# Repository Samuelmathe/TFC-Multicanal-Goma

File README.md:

# TFC Multicanal Goma

Système embarqué IoT de sous-comptage électrique multicanal (ESP32),
développé dans le cadre d'un Travail de Fin de Cycle (ULPGL) : un boîtier
mesure et facture séparément la consommation électrique de plusieurs
locataires branchés sur une même installation, avec coupure automatique par
crédit prépayé et consultation via une application mobile Flutter.

## État du projet

- **Maquette physique** : construite, soudée sur carte perforée et
  **validée sur matériel réel** (4 canaux : 1 bailleur + 3 locataires,
  capteurs simulés par des potentiomètres). C'est cette maquette qui a servi
  à la validation présentée dans le mémoire.
- **Application mobile Flutter** : développée et testée en conditions
  réelles (connexion Wi-Fi à l'ESP32 depuis un téléphone Android).
- **PCB (circuit imprimé, 8 canaux, capteurs ACS712/ZMPT101B réels)** :
  conçu sous KiCad (dossier `kicad/`) — **routage non terminé, il reste 10
  pistes à tracer** ; non encore fabriqué ni assemblé. Le firmware cible pour
  ce PCB (`firmware_pcb_capteurs_reels/`) est écrit et compile, mais n'a donc
  pas pu être testé sur le matériel réel.

## Structure du dépôt

```
firmware/                      -> firmware de la maquette physique (4 canaux,
                                   potentiometres) - construit et valide
firmware_pcb_capteurs_reels/    -> firmware cible pour le PCB (8 canaux,
                                    ACS712 + ZMPT101B) - PCB pas encore
                                    fabrique, code non teste sur materiel reel
application/                     -> application mobile Flutter (Android/iOS)
kicad/                            -> conception du circuit imprime (PCB, 8 canaux)
rapport/                           -> memoire de TFC
presentation/                       -> support de soutenance
```

Chaque dossier de firmware a son propre `README.md` avec le détail de ce qui
a été testé ou non.

## Démarrer

- Firmware maquette : `cd firmware && pio run --target upload` (ESP32 branché
  en USB) — voir `GUIDE_ASSEMBLAGE_ET_FLASH.md` et `GUIDE_MAQUETTE_BOITIER.md`
  à la racine pour le montage physique.
- Application mobile : `cd application && flutter run` (ou `build_apk.sh`
  pour générer un APK).

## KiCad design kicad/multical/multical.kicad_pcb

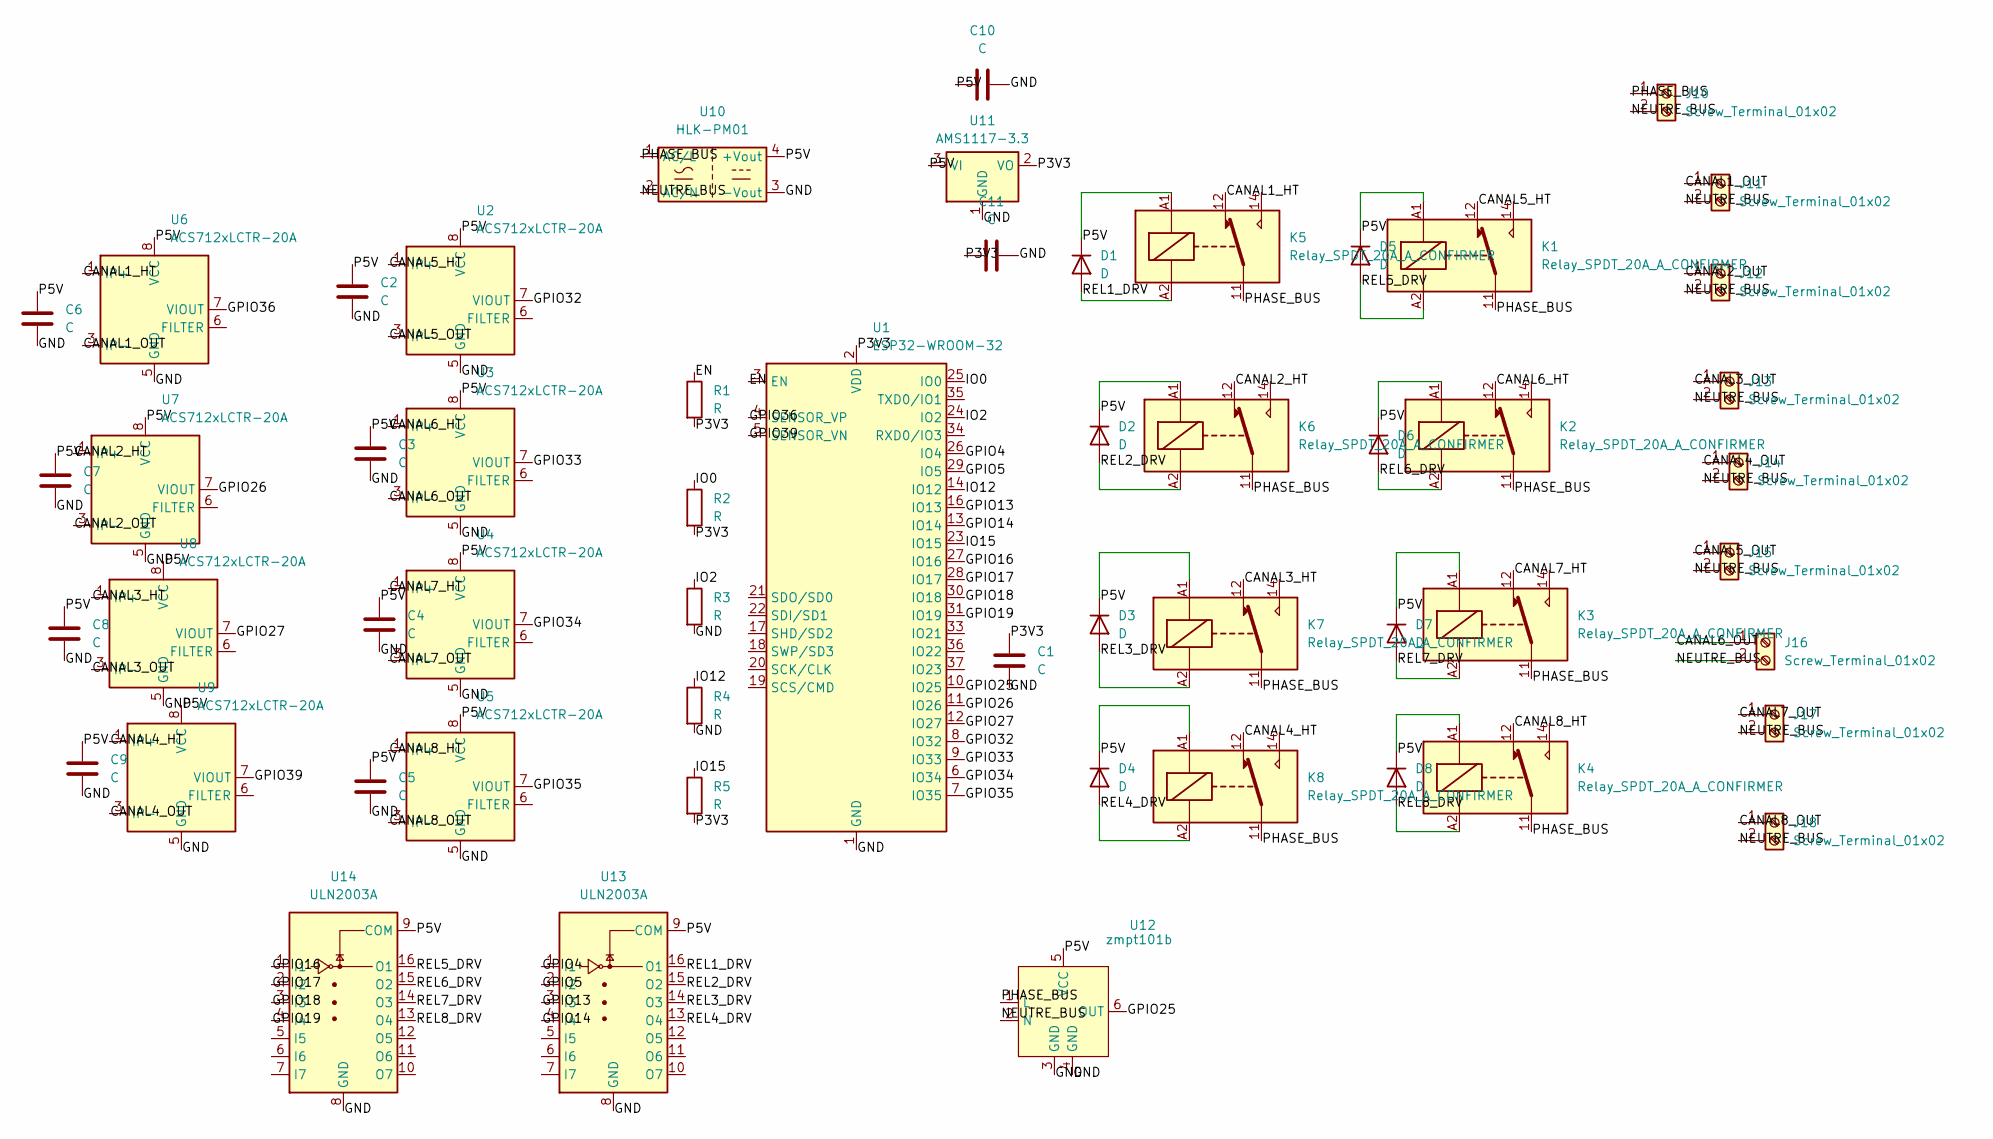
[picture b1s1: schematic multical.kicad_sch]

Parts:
C1, C2, C3, C4, C5, C6, C7, C8, C9: C; C_Disc_D5.0mm_W2.5mm_P5.00mm
C10, C11: C; CP_Radial_D5.0mm_P2.00mm
D1, D2, D3, D4, D5, D6, D7, D8: D; D_DO-41_SOD81_P7.62mm_Horizontal
J10, J11, J12, J13, J14, J15, J16, J17, J18: Screw_Terminal_01x02; TerminalBlock_MaiXu_MX126-5.0-02P_1x02_P5.00mm
K1, K2, K3, K4, K5, K6, K7, K8: Relay_SPDT_20A_A_CONFIRMER; Relay_SPDT_Hongfa_JQC-3FF_0XX-1Z
R1, R2, R3, R4, R5: R; R_Axial_DIN0207_L6.3mm_D2.5mm_P10.16mm_Horizontal
U1: ESP32-WROOM-32
U2, U3, U4, U5, U6, U7, U8, U9: ACS712xLCTR-20A; SOIC-8_3.9x4.9mm_P1.27mm
U10: HLK-PM01; Converter_ACDC_Hi-Link_HLK-PMxx
U11: AMS1117-3.3; SOT-223-3_TabPin2
U12: zmpt101b; PinHeader_1x06_P2.54mm_Vertical
U13, U14: ULN2003A; DIP-16_W7.62mm

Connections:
/CANAL1_HT: K5.12, U6.1 (IP+), U6.2 (IP+)
/CANAL1_OUT: J11.1, U6.3 (IP-), U6.4 (IP-)
/CANAL2_HT: K6.12, U7.1 (IP+), U7.2 (IP+)
/CANAL2_OUT: J12.1, U7.3 (IP-), U7.4 (IP-)
/CANAL3_HT: K7.12, U8.1 (IP+), U8.2 (IP+)
/CANAL3_OUT: J13.1, U8.3 (IP-), U8.4 (IP-)
/CANAL4_HT: K8.12, U9.1 (IP+), U9.2 (IP+)
/CANAL4_OUT: J14.1, U9.3 (IP-), U9.4 (IP-)
/CANAL5_HT: K1.12, U2.1 (IP+), U2.2 (IP+)
/CANAL5_OUT: J15.1, U2.3 (IP-), U2.4 (IP-)
/CANAL6_HT: K2.12, U3.1 (IP+), U3.2 (IP+)
/CANAL6_OUT: J16.1, U3.3 (IP-), U3.4 (IP-)
/CANAL7_HT: K3.12, U4.1 (IP+), U4.2 (IP+)
/CANAL7_OUT: J17.1, U4.3 (IP-), U4.4 (IP-)
/CANAL8_HT: K4.12, U5.1 (IP+), U5.2 (IP+)
/CANAL8_OUT: J18.1, U5.3 (IP-), U5.4 (IP-)
/EN: R1.1, U1.3 (EN)
/GND: C1.2, C2.2, C3.2, C4.2, C5.2, C6.2, C7.2, C8.2, C9.2, C10.2, C11.2, R3.2, R4.2, U1.1 (GND), U1.15 (GND), U1.38 (GND), U1.39 (GND), U2.5 (GND), U3.5 (GND), U4.5 (GND), U5.5 (GND), U6.5 (GND), U7.5 (GND), U8.5 (GND), U9.5 (GND), U10.3 (-Vout), U11.1 (GND), U12.3 (GND), U12.4 (GND), U13.8 (GND), U14.8 (GND)
/GPIO4: U1.26 (IO4), U13.1 (I1)
/GPIO5: U1.29 (IO5), U13.2 (I2)
/GPIO13: U1.16 (IO13), U13.3 (I3)
/GPIO14: U1.13 (IO14), U13.4 (I4)
/GPIO16: U1.27 (IO16), U14.1 (I1)
/GPIO17: U1.28 (IO17), U14.2 (I2)
/GPIO18: U1.30 (IO18), U14.3 (I3)
/GPIO19: U1.31 (IO19), U14.4 (I4)
/GPIO25: U1.10 (IO25), U12.6 (OUT)
/GPIO26: U1.11 (IO26), U7.7 (VIOUT)
/GPIO27: U1.12 (IO27), U8.7 (VIOUT)
/GPIO32: U1.8 (IO32), U2.7 (VIOUT)
/GPIO33: U1.9 (IO33), U3.7 (VIOUT)
/GPIO34: U1.6 (IO34), U4.7 (VIOUT)
/GPIO35: U1.7 (IO35), U5.7 (VIOUT)
/GPIO36: U1.4 (SENSOR_VP), U6.7 (VIOUT)
/GPIO39: U1.5 (SENSOR_VN), U9.7 (VIOUT)
/IO0: R2.1, U1.25 (IO0)
/IO2: R3.1, U1.24 (IO2)
/IO12: R4.1, U1.14 (IO12)
/IO15: R5.1, U1.23 (IO15)
/NEUTRE_BUS: J10.2, J11.2, J12.2, J13.2, J14.2, J15.2, J16.2, J17.2, J18.2, U10.2 (AC/N), U12.2 (N)
/P3V3: C1.1, C11.1, R1.2, R2.2, R5.2, U1.2 (VDD), U11.2 (VO)
/P5V: C2.1, C3.1, C4.1, C5.1, C6.1, C7.1, C8.1, C9.1, C10.1, D1.1 (K), D2.1 (K), D3.1 (K), D4.1 (K), D5.1 (K), D6.1 (K), D7.1 (K), D8.1 (K), K1.A1, K2.A1, K3.A1, K4.A1, K5.A1, K6.A1, K7.A1, K8.A1, U2.8 (VCC), U3.8 (VCC), U4.8 (VCC), U5.8 (VCC), U6.8 (VCC), U7.8 (VCC), U8.8 (VCC), U9.8 (VCC), U10.4 (+Vout), U11.3 (VI), U12.5 (VCC), U13.9 (COM), U14.9 (COM)
/PHASE_BUS: J10.1, K1.11, K2.11, K3.11, K4.11, K5.11, K6.11, K7.11, K8.11, U10.1 (AC/L), U12.1 (L)
/REL1_DRV: D1.2 (A), K5.A2, U13.16 (O1)
/REL2_DRV: D2.2 (A), K6.A2, U13.15 (O2)
/REL3_DRV: D3.2 (A), K7.A2, U13.14 (O3)
/REL4_DRV: D4.2 (A), K8.A2, U13.13 (O4)
/REL5_DRV: D5.2 (A), K1.A2, U14.16 (O1)
/REL6_DRV: D6.2 (A), K2.A2, U14.15 (O2)
/REL7_DRV: D7.2 (A), K3.A2, U14.14 (O3)
/REL8_DRV: D8.2 (A), K4.A2, U14.13 (O4)

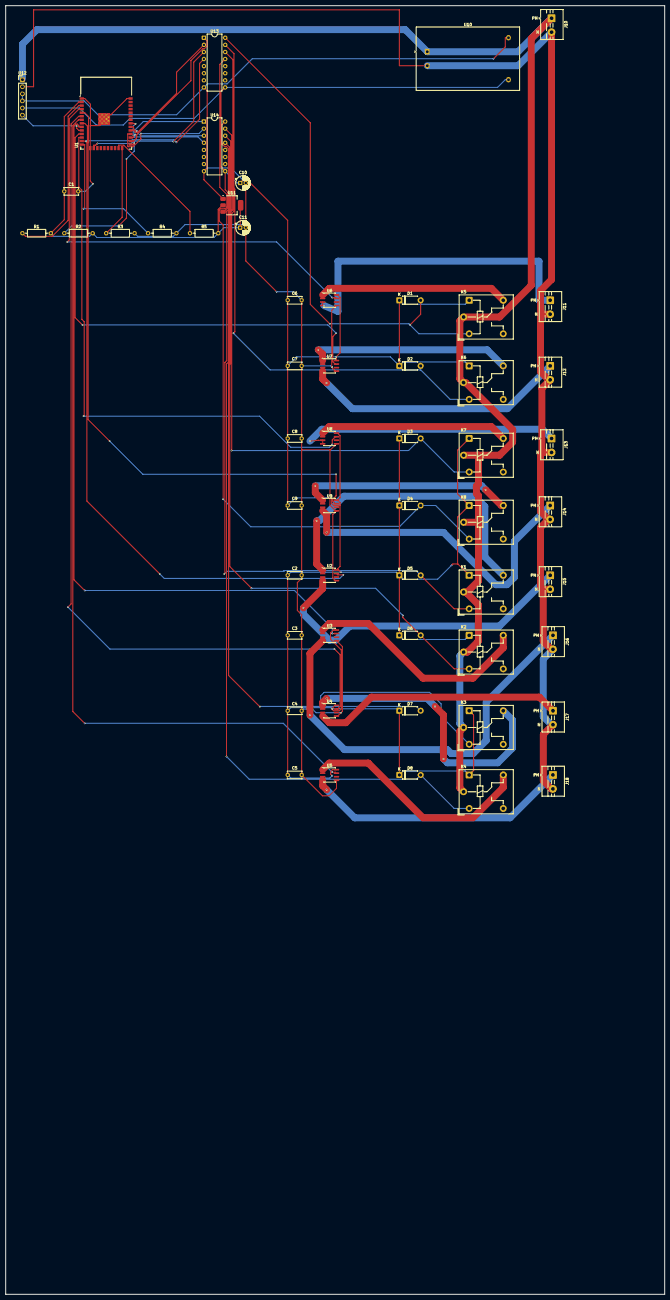
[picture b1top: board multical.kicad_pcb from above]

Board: 2 copper layers, 236.0 x 461.5 mm, 55 parts (0 on the bottom side), 51 nets.

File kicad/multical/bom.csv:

"Références","Valeur","Empreinte","Qté"
"C1-C9","C","Capacitor_THT:C_Disc_D5.0mm_W2.5mm_P5.00mm","9"
"C10,C11","C","Capacitor_THT:CP_Radial_D5.0mm_P2.00mm","2"
"D1-D8","D","Diode_THT:D_DO-41_SOD81_P7.62mm_Horizontal","8"
"J10-J17","Screw_Terminal_01x02","TerminalBlock:TerminalBlock_MaiXu_MX126-5.0-02P_1x02_P5.00mm","8"
"J18","Screw_Terminal_01x02","TerminalBlock_MaiXu_MX126-5.0-02P_1x02_P5.00mm","1"
"K1-K8","Relay_SPDT","Relay_THT:Relay_SPDT_Hongfa_JQC-3FF_0XX-1Z","8"
"R1-R5","R","Resistor_THT:R_Axial_DIN0207_L6.3mm_D2.5mm_P10.16mm_Horizontal","5"
"U1","ESP32-WROOM-32","RF_Module:ESP32-WROOM-32","1"
"U2-U9","ACS712xLCTR-20A","Package_SO:SOIC-8_3.9x4.9mm_P1.27mm","8"
"U10","HLK-PM01","Converter_ACDC:Converter_ACDC_Hi-Link_HLK-PMxx","1"
"U11","AMS1117-3.3","Package_TO_SOT_SMD:SOT-223-3_TabPin2","1"
"U12","zmpt101b","Connector_PinHeader_2.54mm:PinHeader_1x06_P2.54mm_Vertical","1"
"U13,U14","ULN2003A","Package_DIP:DIP-16_W7.62mm","2"

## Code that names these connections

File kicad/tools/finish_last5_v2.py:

import uuid

FILE = "/home/samuel/Documents/TFC-Multicanal-Goma/kicad/multical/multical.kicad_pcb"

with open(FILE, encoding="utf-8") as f:
    content = f.read()

def seg(x1, y1, x2, y2, width, layer, net):
    return (
        '\t(segment\n'
        f'\t\t(start {x1:.4f} {y1:.4f})\n'
        f'\t\t(end {x2:.4f} {y2:.4f})\n'
        f'\t\t(width {width})\n'
        f'\t\t(layer "{layer}")\n'
        f'\t\t(net "{net}")\n'
        f'\t\t(uuid "{uuid.uuid4()}")\n'
        '\t)\n'
    )

def via(x, y, size, drill, net):
    return (
        '\t(via\n'
        f'\t\t(at {x:.4f} {y:.4f})\n'
        f'\t\t(size {size})\n'
        f'\t\t(drill {drill})\n'
        '\t\t(layers "F.Cu" "B.Cu")\n'
        f'\t\t(net "{net}")\n'
        f'\t\t(uuid "{uuid.uuid4()}")\n'
        '\t)\n'
    )

items = []

# --- CANAL1_OUT : U6 (SMD, pitch 1.27mm -> taper fin) -> via -> B.Cu large -> J11 ---
# x=133 choisi pour eviter la diagonale GPIO36 (B.Cu, se termine a x=130.97)
items.append(seg(127.525, 124.635, 127.525, 125.905, 0.3, "F.Cu", "/CANAL1_OUT"))  # pin3-pin4
items.append(seg(127.525, 125.905, 133.0, 128.0, 0.3, "F.Cu", "/CANAL1_OUT"))       # taper vers via
items.append(via(133.0, 128.0, 0.6, 0.3, "/CANAL1_OUT"))
items.append(seg(133.0, 128.0, 133.0, 110.0, 2.5, "B.Cu", "/CANAL1_OUT"))
items.append(seg(133.0, 110.0, 205.0, 110.0, 2.5, "B.Cu", "/CANAL1_OUT"))
items.append(seg(205.0, 110.0, 205.0, 124.0, 2.5, "B.Cu", "/CANAL1_OUT"))
items.append(seg(205.0, 124.0, 209.0, 124.0, 2.5, "B.Cu", "/CANAL1_OUT"))

# --- CANAL3_OUT : bout de piste existant (B.Cu) -> via -> F.Cu -> U8 pin3/pin4 (SMD F.Cu uniquement) ---
items.append(via(122.9657, 174.4434, 0.6, 0.3, "/CANAL3_OUT"))
items.append(seg(122.9657, 174.4434, 126.0, 174.135, 0.3, "F.Cu", "/CANAL3_OUT"))
items.append(seg(126.0, 174.135, 127.525, 174.135, 0.3, "F.Cu", "/CANAL3_OUT"))
items.append(seg(127.525, 174.135, 127.525, 175.405, 0.3, "F.Cu", "/CANAL3_OUT"))

# --- NEUTRE_BUS : U12 pin2 -> fin (evite pin1 a 2.54mm) -> bus existant pres du HLK ---
items.append(seg(20.0, 47.54, 24.0, 47.54, 0.3, "F.Cu", "/NEUTRE_BUS"))   # sort horizontalement, loin de pin1 (au-dessus)
items.append(seg(24.0, 47.54, 24.0, 20.0, 0.3, "F.Cu", "/NEUTRE_BUS"))
items.append(seg(24.0, 20.0, 155.0, 20.0, 0.3, "F.Cu", "/NEUTRE_BUS"))
items.append(seg(155.0, 20.0, 155.0, 40.0, 0.3, "F.Cu", "/NEUTRE_BUS"))
items.append(seg(155.0, 40.0, 165.0, 40.0, 0.3, "F.Cu", "/NEUTRE_BUS"))

marker = "\t(embedded_fonts no)\n)"
assert content.count(marker) == 1
block = "\n" + "".join(items)
content = content.replace(marker, block + marker)

with open(FILE, "w", encoding="utf-8") as f:
    f.write(content)

print(f"OK: {len(items)} elements ajoutes")
